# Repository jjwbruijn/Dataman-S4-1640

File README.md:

# Dataman-S4-1640
A 40-pin adapter for the Dataman S4 EPROM Programmer 

Allows you to program 16-bits 40 pin EPROMs with your S4 programmer. You'll need a copy of Eagle PCB to open these files.

Parts needed: 
- 18x 1k 0805 resistors
- 5x 100nF 1206
- 5x 74xx573 SMD (SO-20)

Errata:
- There needs to a 1k resistor in series with both the UPPER and LOWER data line. Please refer to the schematic and find a spot on the PCB to put it, maybe cut a trace. Or just fix it on the board :)

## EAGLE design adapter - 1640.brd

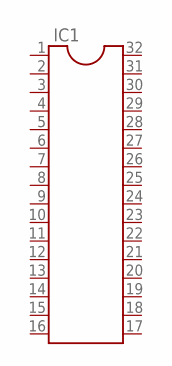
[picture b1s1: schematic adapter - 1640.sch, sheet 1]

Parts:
IC1: DIL32

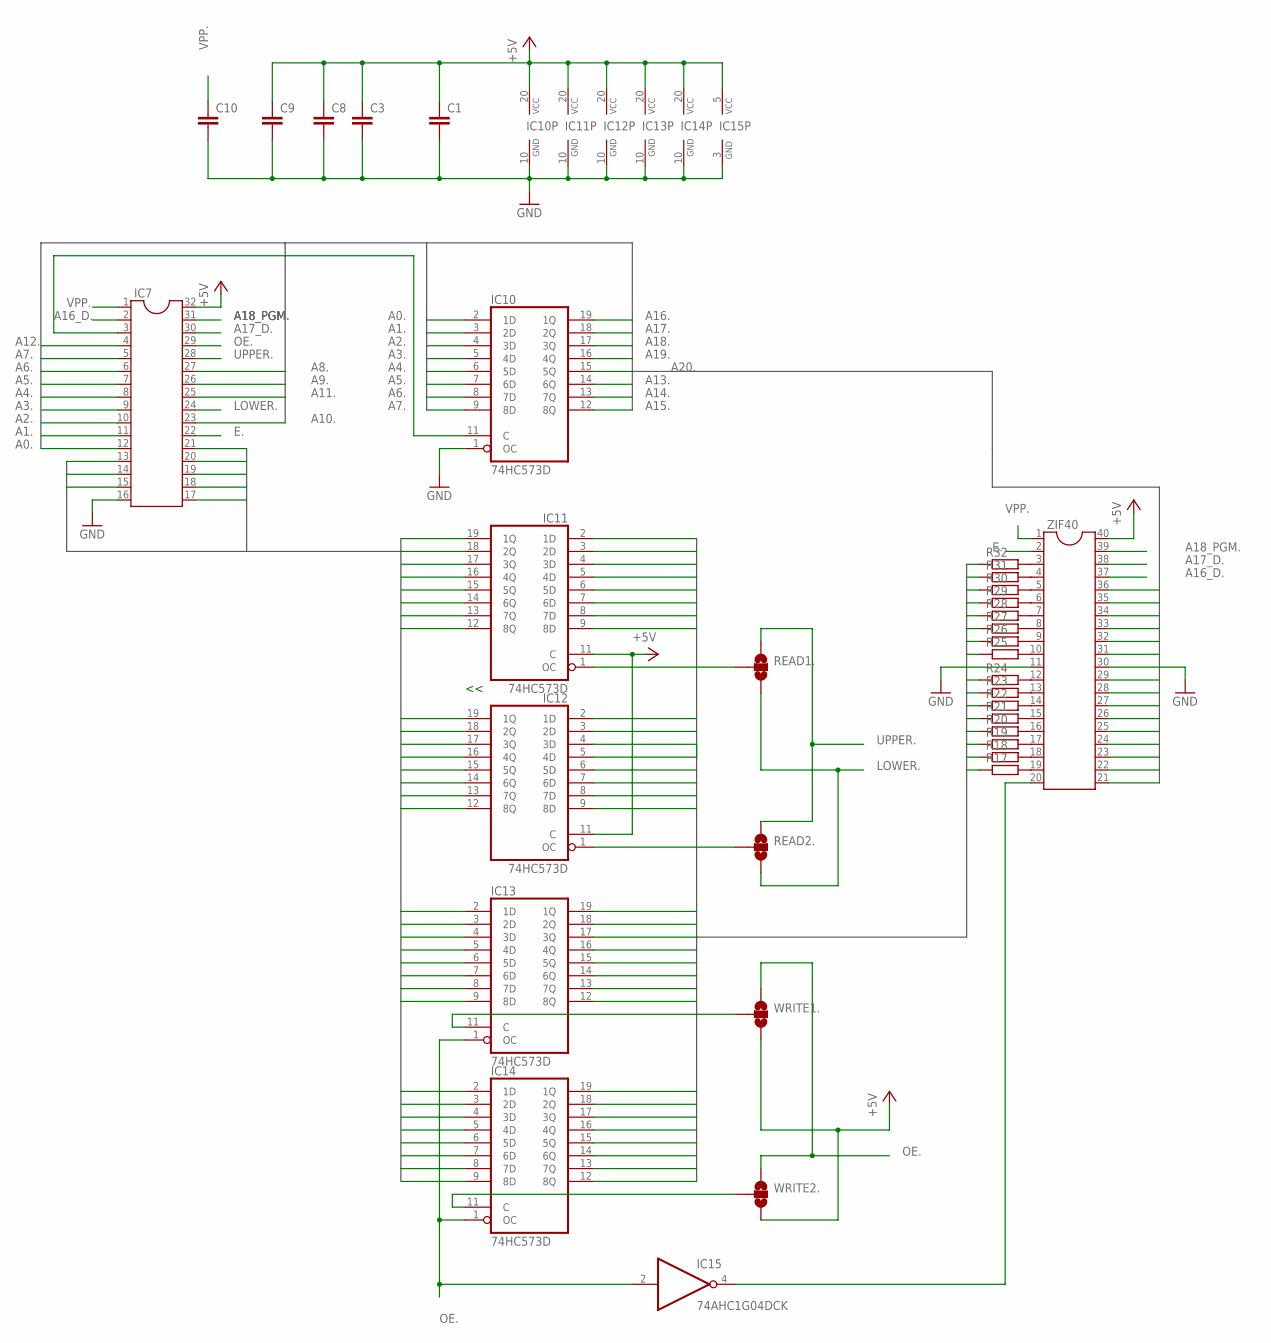
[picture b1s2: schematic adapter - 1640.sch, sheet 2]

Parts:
C1, C3, C8, C9, C10: C-EUC1206; C1206
IC7: DIL32
IC10, IC11, IC12, IC13, IC14: 74HC573D; SO20W
IC15: 74AHC1G04DCK; SC70-5
R17, R18, R19, R20, R21, R22, R23, R24, R25, R26, R27, R28, R29, R30, R31, R32: R-EU_R0805; R0805
READ1., READ2.: JUMPER-PAD-3-NOYES_SILK; PAD-JUMPER-3-NO_YES_SILK
WRITE1., WRITE2.: JUMPER-PAD-3-NOYES_SILK; PAD-JUMPER-3-NO_YES_SILK
ZIF40: DIL40

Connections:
+5V.: C1.1, C3.1, C8.1, C9.1, IC7.32, IC10.20 (VCC), IC11.11 (C), IC11.20 (VCC), IC12.11 (C), IC12.20 (VCC), IC13.20 (VCC), IC14.20 (VCC), IC15.5 (VCC), WRITE1..3, WRITE2..3, ZIF40.40
A0.: IC7.12, IC10.2 (1D)
A1.: IC7.11, IC10.3 (2D), ZIF40.21
A2.: IC7.10, IC10.4 (3D), ZIF40.22
A3.: IC7.9, IC10.5 (4D), ZIF40.23
A4.: IC7.8, IC10.6 (5D), ZIF40.24
A5.: IC7.7, IC10.7 (6D), ZIF40.25
A6.: IC7.6, IC10.8 (7D), ZIF40.26
A7.: IC7.5, IC10.9 (8D), ZIF40.27
A8.: IC7.27, ZIF40.28
A9.: IC7.26, ZIF40.29
A10.: IC7.23, ZIF40.31
A11.: IC7.25, ZIF40.32
A12.: IC7.4, ZIF40.33
A13.: IC10.14 (6Q), ZIF40.34
A14.: IC10.13 (7Q), ZIF40.35
A15.: IC10.12 (8Q), ZIF40.36
A16.: IC10.19 (1Q)
A16_D.: IC7.2, ZIF40.37
A17.: IC10.18 (2Q)
A17_D.: IC7.30, ZIF40.38
A18.: IC10.17 (3Q)
A18_PGM.: IC7.31, ZIF40.39
A19.: IC10.16 (4Q)
A20.: IC10.15 (5Q)
D0.: IC7.13, IC11.19 (1Q), IC12.19 (1Q), IC13.2 (1D), IC14.2 (1D)
D1.: IC7.14, IC11.18 (2Q), IC12.18 (2Q), IC13.3 (2D), IC14.3 (2D)
D2.: IC7.15, IC11.17 (3Q), IC12.17 (3Q), IC13.4 (3D), IC14.4 (3D)
D3.: IC7.17, IC11.16 (4Q), IC12.16 (4Q), IC13.5 (4D), IC14.5 (4D)
D4.: IC7.18, IC11.15 (5Q), IC12.15 (5Q), IC13.6 (5D), IC14.6 (5D)
D5.: IC7.19, IC11.14 (6Q), IC12.14 (6Q), IC13.7 (6D), IC14.7 (6D)
D6.: IC7.20, IC11.13 (7Q), IC12.13 (7Q), IC13.8 (7D), IC14.8 (7D)
D7.: IC7.21, IC11.12 (8Q), IC12.12 (8Q), IC13.9 (8D), IC14.9 (8D)
E.: IC7.22, ZIF40.2
GND.: C1.2, C3.2, C8.2, C9.2, C10.2, IC7.16, IC10.1 (OC), IC10.10 (GND), IC11.10 (GND), IC12.10 (GND), IC13.10 (GND), IC14.10 (GND), IC15.3 (GND), ZIF40.11, ZIF40.30
LOWER.: IC7.24, READ1..3, READ2..3
unnamed: IC7.3, IC10.11 (C)
unnamed: IC11.1 (OC), READ1..2
unnamed: IC12.1 (OC), READ2..2
unnamed: IC13.11 (C), WRITE1..2
unnamed: IC14.11 (C), WRITE2..2
unnamed: IC15.4 (O), ZIF40.20
unnamed: R31.2, ZIF40.4
unnamed: R32.2, ZIF40.3
unnamed: R30.2, ZIF40.5
unnamed: R29.2, ZIF40.6
unnamed: R28.2, ZIF40.7
unnamed: R27.2, ZIF40.8
unnamed: R26.2, ZIF40.9
unnamed: R25.2, ZIF40.10
unnamed: R24.2, ZIF40.12
unnamed: R23.2, ZIF40.13
unnamed: R22.2, ZIF40.14
unnamed: R21.2, ZIF40.15
unnamed: R20.2, ZIF40.16
unnamed: R19.2, ZIF40.17
unnamed: R18.2, ZIF40.18
unnamed: R17.2, ZIF40.19
OE.: IC7.29, IC13.1 (OC), IC14.1 (OC), IC15.2 (I), WRITE1..1, WRITE2..1
Q0.: IC11.2 (1D), IC13.19 (1Q), R17.1
Q1.: IC11.3 (2D), IC13.18 (2Q), R18.1
Q2.: IC11.4 (3D), IC13.17 (3Q), R19.1
Q3.: IC11.5 (4D), IC13.16 (4Q), R20.1
Q4.: IC11.6 (5D), IC13.15 (5Q), R21.1
Q5.: IC11.7 (6D), IC13.14 (6Q), R22.1
Q6.: IC11.8 (7D), IC13.13 (7Q), R23.1
Q7.: IC11.9 (8D), IC13.12 (8Q), R24.1
Q8.: IC12.2 (1D), IC14.19 (1Q), R25.1
Q9.: IC12.3 (2D), IC14.18 (2Q), R26.1
Q10.: IC12.4 (3D), IC14.17 (3Q), R27.1
Q11.: IC12.5 (4D), IC14.16 (4Q), R28.1
Q12.: IC12.6 (5D), IC14.15 (5Q), R29.1
Q13.: IC12.7 (6D), IC14.14 (6Q), R30.1
Q14.: IC12.8 (7D), IC14.13 (7Q), R31.1
Q15.: IC12.9 (8D), IC14.12 (8Q), R32.1
UPPER.: IC7.28, READ1..1, READ2..1
VPP.: C10.1, IC7.1, ZIF40.1

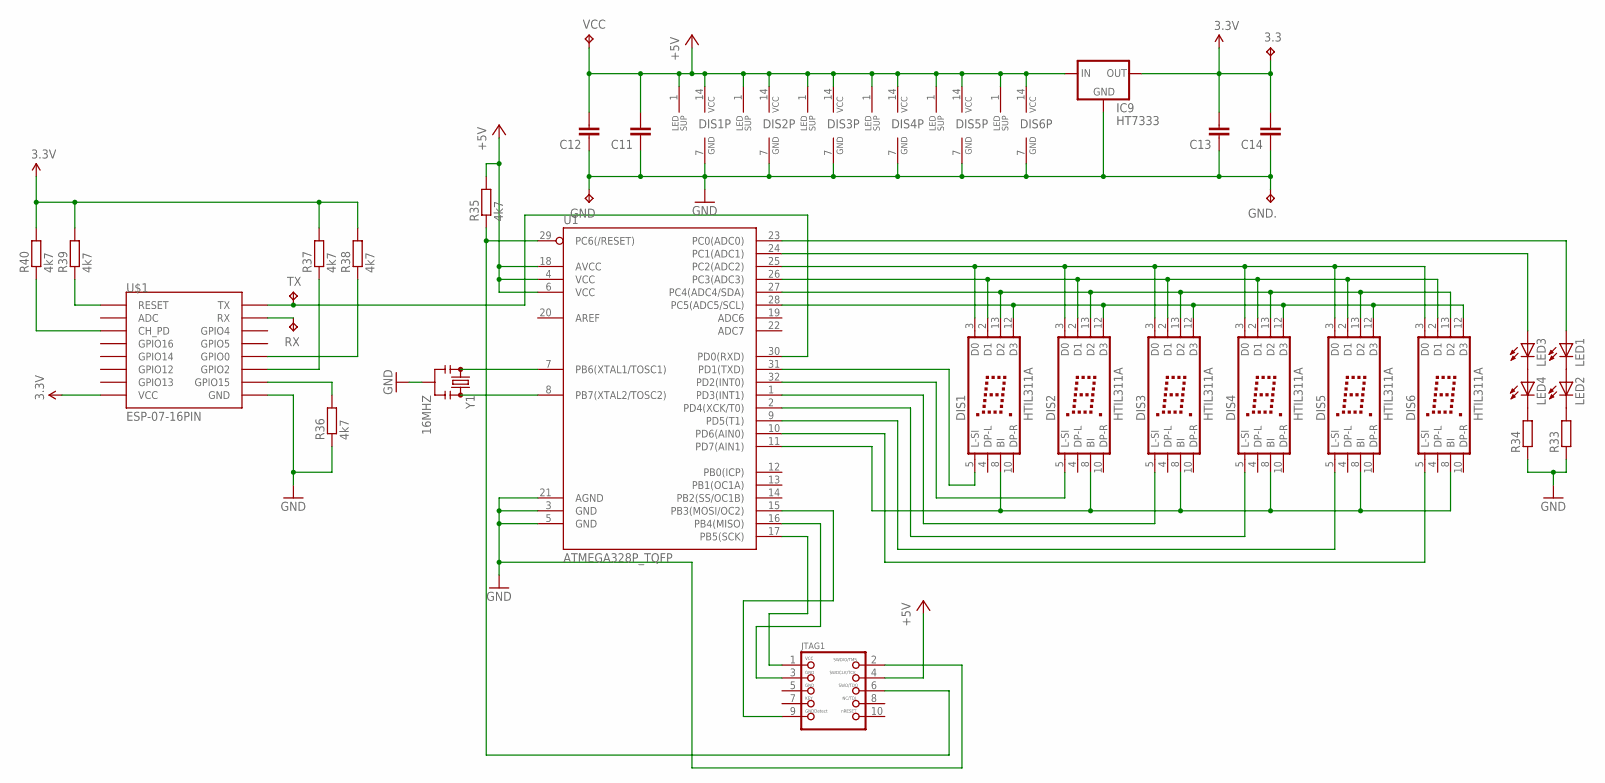
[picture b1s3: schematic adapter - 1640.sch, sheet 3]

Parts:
3.3: TPTP15SQ; TP15SQ
C11, C12, C13, C14: C-EUC1206; C1206
DIS1, DIS2, DIS3, DIS4, DIS5, DIS6: HTIL311A
GND, GND.: TPTP15SQ; TP15SQ
IC9: HT7333; SOT-89
JTAG1: JTAG-CORTEXM3; 2X05_1.27MM_SMT
LED1, LED2, LED3, LED4: LED-0603; LED-603
R33, R34: R-EU_M1206; M1206
R35, R36, R37, R38, R39, R40: 4k7; M1206
RX: TPTP15SQ; TP15SQ
TX: TPTP15SQ; TP15SQ
U1: ATMEGA328P_TQFP; TQFP32-08
U$1: ESP-07-16PIN
VCC: TPTP15SQ; TP15SQ
Y1: 16MHZ; RESONATOR-SMD

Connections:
3.3V: 3.3.TP, C13.2, C14.2, IC9.1 (OUT), R37.2, R38.2, R39.2, R40.2, U$1.VCC
+5V.2: C11.2, C12.2, DIS1.1 (LEDSUP), DIS1.14 (VCC), DIS2.1 (LEDSUP), DIS2.14 (VCC), DIS3.1 (LEDSUP), DIS3.14 (VCC), DIS4.1 (LEDSUP), DIS4.14 (VCC), DIS5.1 (LEDSUP), DIS5.14 (VCC), DIS6.1 (LEDSUP), DIS6.14 (VCC), IC9.3 (IN), IC9.4 (IN), JTAG1.4, R35.2, U1.4 (VCC), U1.6 (VCC), U1.18 (AVCC), VCC.TP
GND.2: C11.1, C12.1, C13.1, C14.1, DIS1.7 (GND), DIS2.7 (GND), DIS3.7 (GND), DIS4.7 (GND), DIS5.7 (GND), DIS6.7 (GND), GND.TP, GND..TP, IC9.2 (GND), JTAG1.2, R33.1, R34.1, R36.1, U1.3 (GND), U1.5 (GND), U1.21 (AGND), U$1.GND, Y1.2
unnamed: DIS1.3 (D0), DIS2.3 (D0), DIS3.3 (D0), DIS4.3 (D0), DIS5.3 (D0), DIS6.3 (D0), U1.25 (PC2(ADC2))
unnamed: DIS1.2 (D1), DIS2.2 (D1), DIS3.2 (D1), DIS4.2 (D1), DIS5.2 (D1), DIS6.2 (D1), U1.26 (PC3(ADC3))
unnamed: DIS1.13 (D2), DIS2.13 (D2), DIS3.13 (D2), DIS4.13 (D2), DIS5.13 (D2), DIS6.13 (D2), U1.27 (PC4(ADC4/SDA))
unnamed: DIS1.12 (D3), DIS2.12 (D3), DIS3.12 (D3), DIS4.12 (D3), DIS5.12 (D3), DIS6.12 (D3), U1.28 (PC5(ADC5/SCL))
unnamed: DIS1.8 (BI), DIS2.8 (BI), DIS3.8 (BI), DIS4.8 (BI), DIS5.8 (BI), DIS6.8 (BI), U1.11 (PD7(AIN1))
unnamed: LED1.C, LED2.A
unnamed: LED3.C, LED4.A
unnamed: LED4.C, R34.2
unnamed: LED2.C, R33.2
unnamed: LED3.A, U1.24 (PC1(ADC1))
unnamed: LED1.A, U1.23 (PC0(ADC0))
unnamed: DIS1.5 (L-SI), U1.31 (PD1(TXD))
unnamed: DIS2.5 (L-SI), U1.32 (PD2(INT0))
unnamed: DIS3.5 (L-SI), U1.1 (PD3(INT1))
unnamed: DIS4.5 (L-SI), U1.2 (PD4(XCK/T0))
unnamed: DIS5.5 (L-SI), U1.9 (PD5(T1))
unnamed: DIS6.5 (L-SI), U1.10 (PD6(AIN0))
unnamed: JTAG1.1, U1.17 (PB5(SCK))
unnamed: JTAG1.6, R35.1, U1.29 (PC6(/RESET))
unnamed: JTAG1.3, U1.16 (PB4(MISO))
unnamed: JTAG1.9, U1.15 (PB3(MOSI/OC2))
unnamed: U1.7 (PB6(XTAL1/TOSC1)), Y1.1
unnamed: U1.8 (PB7(XTAL2/TOSC2)), Y1.3
unnamed: R39.1, U$1.REST (RESET)
unnamed: R40.1, U$1.CH_PD
unnamed: RX.TP, U$1.RX
unnamed: TX.TP, U1.30 (PD0(RXD)), U$1.TX
unnamed: R36.2, U$1.GPIO15
unnamed: R37.1, U$1.GPIO2
unnamed: R38.1, U$1.GPIO0

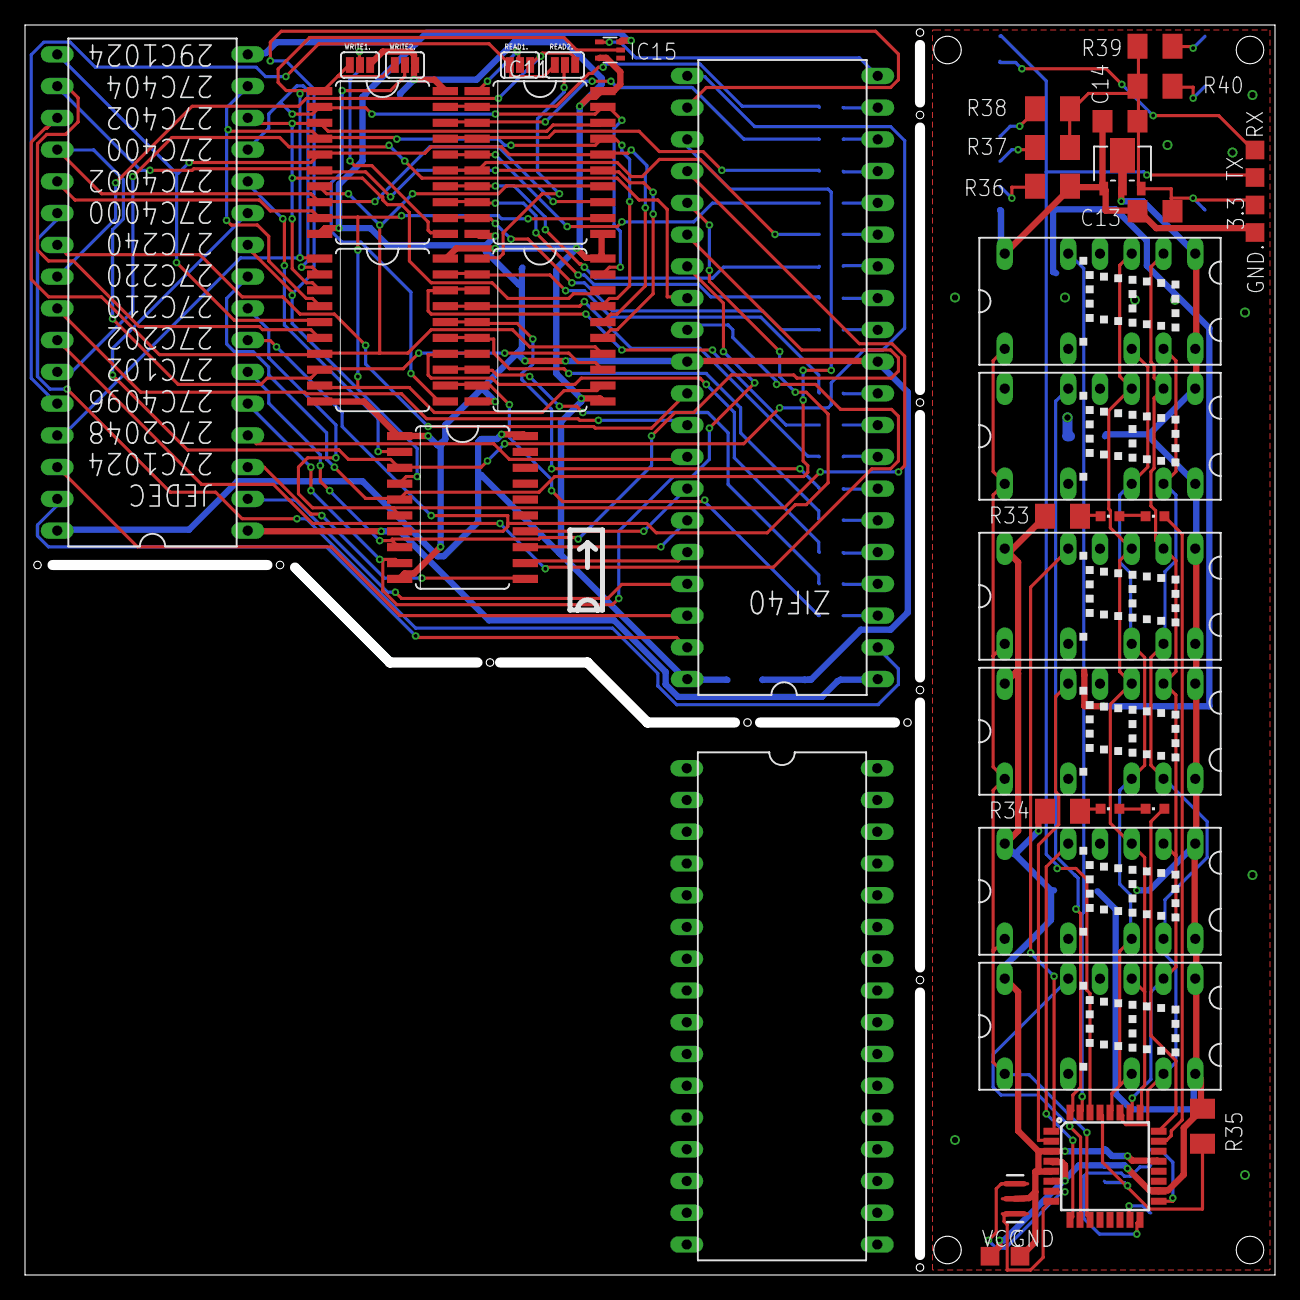
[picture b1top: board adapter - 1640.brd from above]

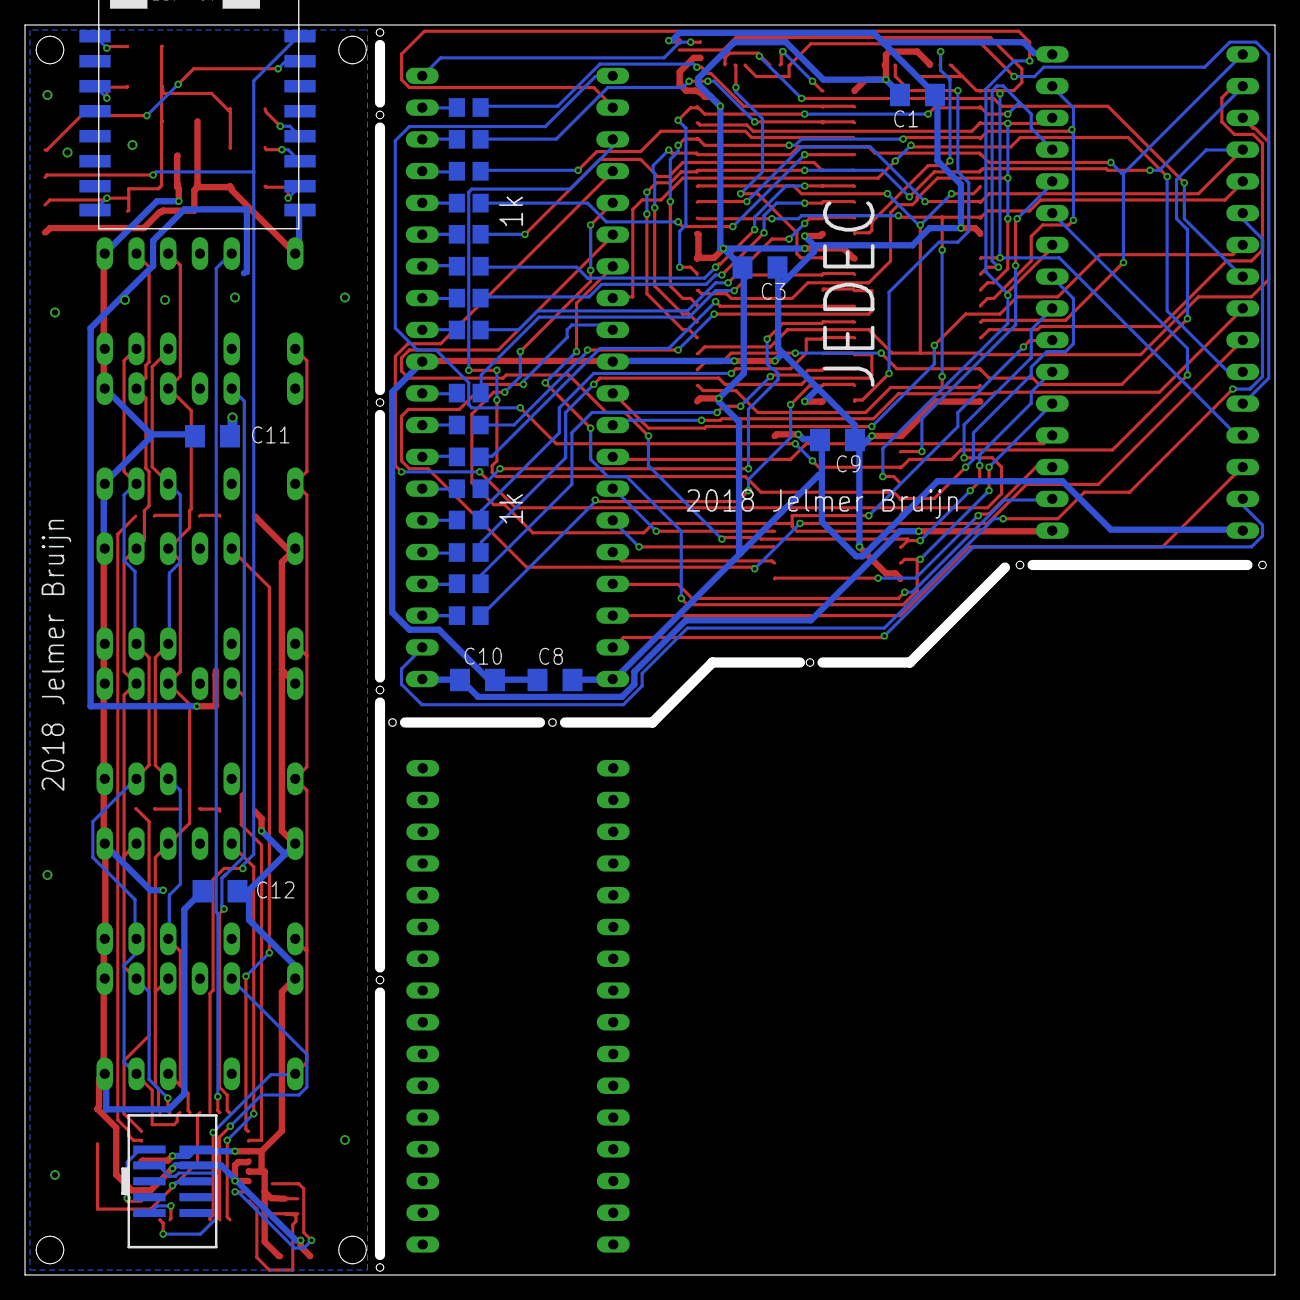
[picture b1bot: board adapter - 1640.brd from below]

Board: 2 copper layers, 99.2 x 99.2 mm, 67 parts (25 on the bottom side), 105 nets.

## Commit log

2018-09-28 Added board and schematic

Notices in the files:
parts and their libraries:
SparkFun-Passives: Licensing: Creative Commons ShareAlike 4.0 International - https://creativecommons.org/licenses/by-sa/4.0
microbuilder: This work is placed in the public domain, and may be freely used for commercial and non-commercial work with the following conditions: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
